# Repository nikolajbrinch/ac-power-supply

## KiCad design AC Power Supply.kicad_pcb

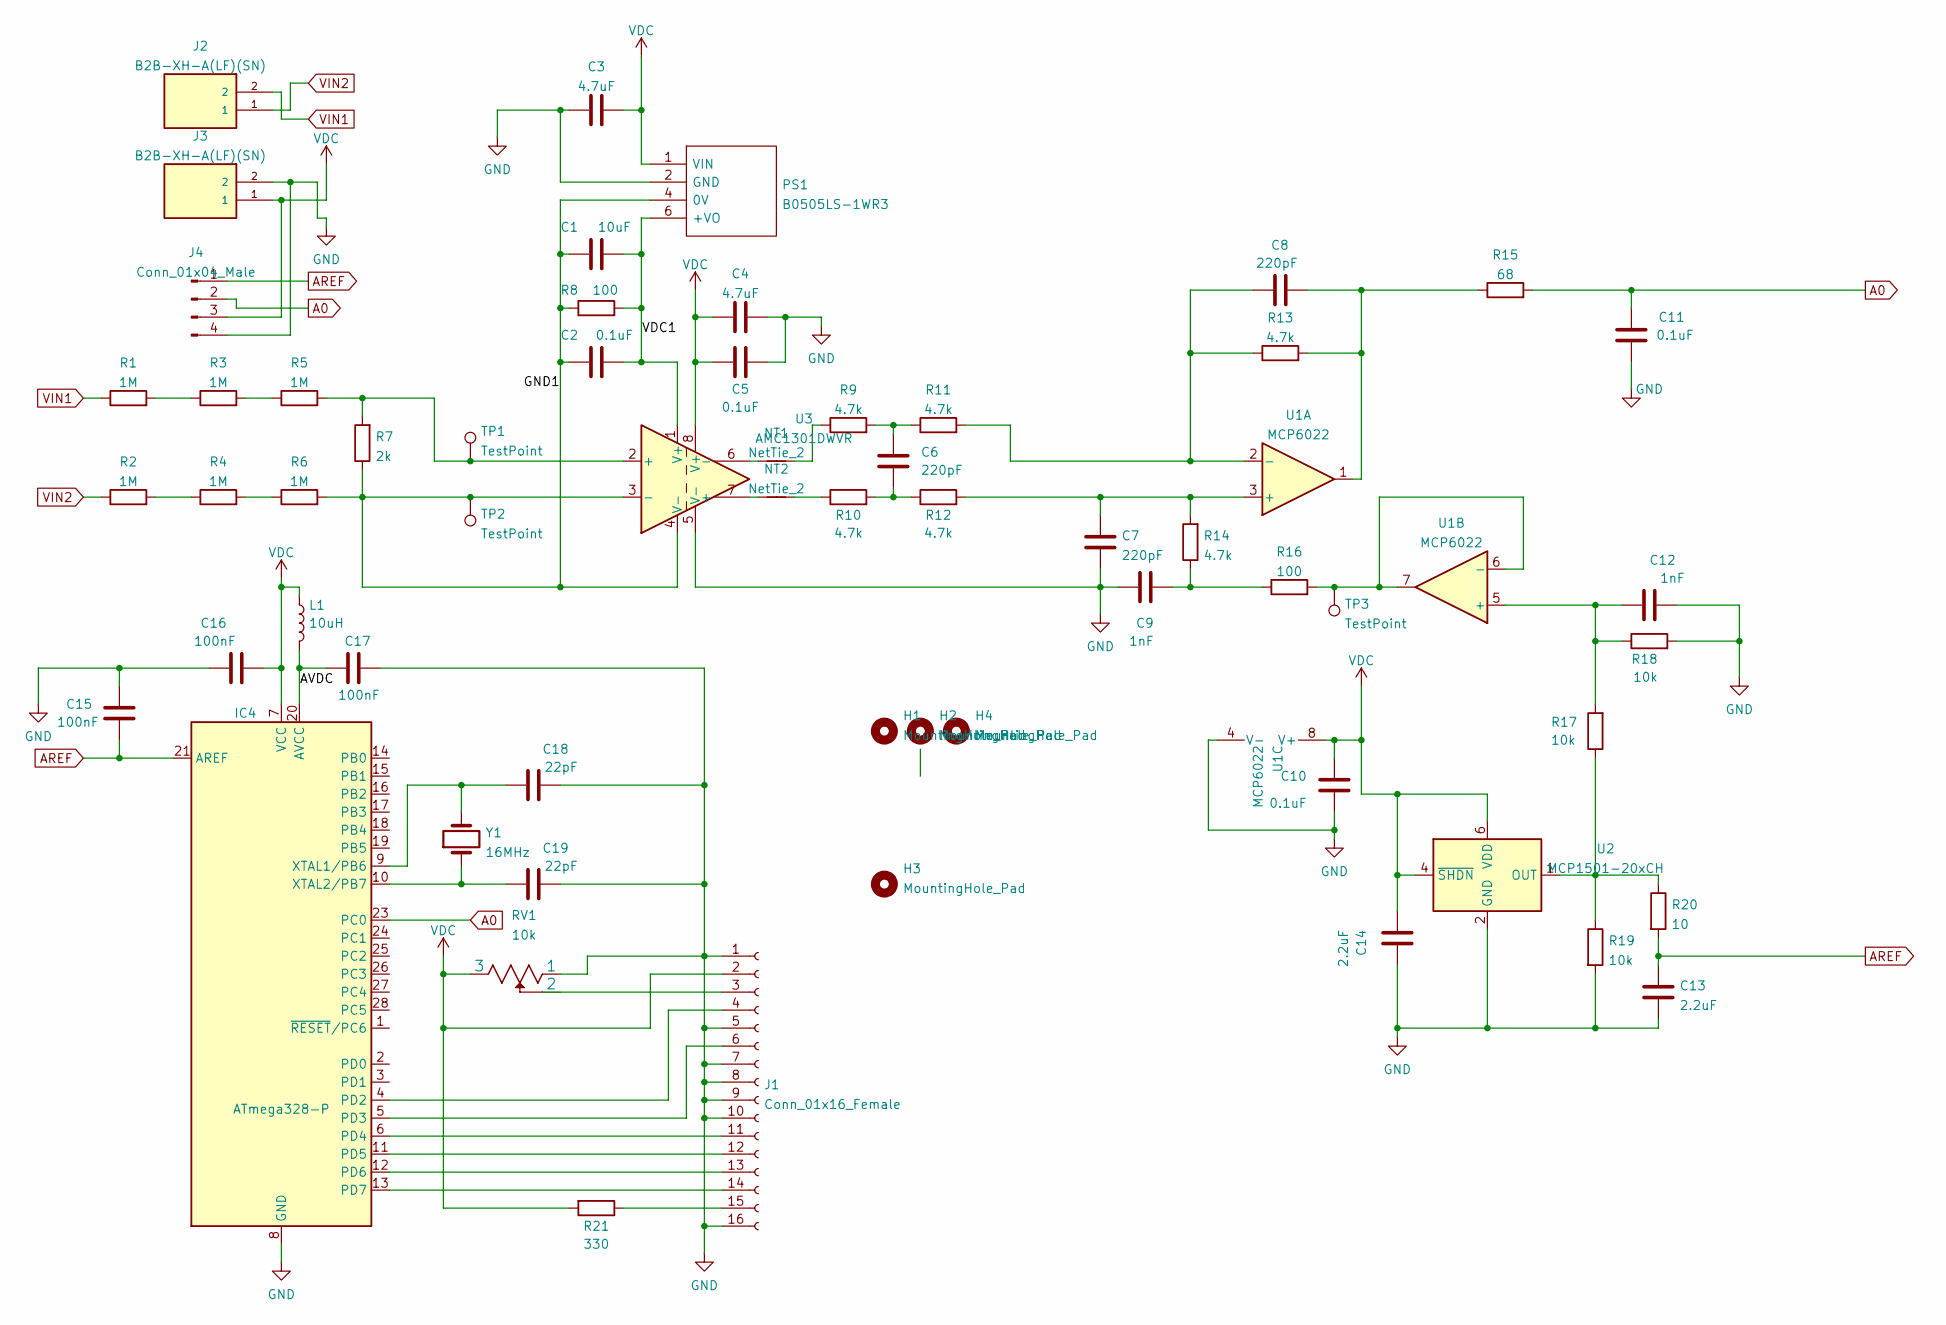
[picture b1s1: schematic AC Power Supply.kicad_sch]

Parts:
C1: 10uF; C_0805_2012Metric_Pad1.18x1.45mm_HandSolder
C2, C5, C10, C11: 0.1uF; C_0805_2012Metric_Pad1.18x1.45mm_HandSolder
C3, C4: 4.7uF; C_0805_2012Metric_Pad1.18x1.45mm_HandSolder
C6, C7, C8: 220pF; C_0805_2012Metric_Pad1.18x1.45mm_HandSolder
C9, C12: 1nF; C_0805_2012Metric_Pad1.18x1.45mm_HandSolder
C13, C14: 2.2uF; C_0805_2012Metric_Pad1.18x1.45mm_HandSolder
C15, C16, C17: 100nF; C_0805_2012Metric_Pad1.18x1.45mm_HandSolder
C18, C19: 22pF; C_0805_2012Metric_Pad1.18x1.45mm_HandSolder
H1, H2, H3, H4: MountingHole_Pad; MountingHole_2.7mm_M2.5_DIN965
IC4: ATmega328-P; DIP-28_W7.62mm_Socket_LongPads
J1: Conn_01x16_Female; PinSocket_1x16_P2.54mm_Vertical
J2, J3: B2B-XH-A(LF)(SN); JST_B2B-XH-A(LF)(SN)
J4: Conn_01x04_Male; PinHeader_1x04_P2.54mm_Vertical
L1: 10uH; L_0805_2012Metric_Pad1.15x1.40mm_HandSolder
NT1, NT2: NetTie_2; NetTie-2_THT_Pad0.3mm
PS1: B0505LS-1WR3; CONV_B0505LS-1WR3; Manufacturer_Part_Number B0505LS-1WR3
R1, R2, R3, R4, R5, R6: 1M; R_1206_3216Metric_Pad1.30x1.75mm_HandSolder
R7: 2k; R_1206_3216Metric_Pad1.30x1.75mm_HandSolder
R8: 100; R_1812_4532Metric_Pad1.30x3.40mm_HandSolder
R9, R10, R11, R12, R13, R14: 4.7k; R_0805_2012Metric_Pad1.20x1.40mm_HandSolder
R15: 68; R_0805_2012Metric_Pad1.20x1.40mm_HandSolder
R16: 100; R_0805_2012Metric_Pad1.20x1.40mm_HandSolder
R17, R18, R19: 10k; R_0805_2012Metric_Pad1.20x1.40mm_HandSolder
R20: 10; R_0805_2012Metric_Pad1.20x1.40mm_HandSolder
R21: 330; R_0805_2012Metric_Pad1.20x1.40mm_HandSolder
RV1: 10k; 64WR10KLF
TP1, TP2, TP3: TestPoint; TestPoint_THTPad_D1.0mm_Drill0.5mm
U1: MCP6022; SOIC-8_3.9x4.9mm_P1.27mm
U2: MCP1501-20xCH; SOT-23-6_Handsoldering
U3: AMC1301DWVR
Y1: 16MHz; Crystal_HC49-4H_Vertical

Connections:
/AVDC: C17.1, IC4.20 (AVCC), L1.2
/GND1: C1.1, C2.1, PS1.4 (0V), R6.2, R7.1, R8.1, TP2.1, U3.3 (-), U3.4 (V-)
/VDC1: C1.2, C2.2, PS1.6 (+VO), R8.2, U3.1 (V+)
A0: C11.2, IC4.23 (PC0), J4.2, R15.2
AREF: C13.1, C15.2, IC4.21 (AREF), J4.1, R20.2
GND: C3.1, C4.1, C5.1, C7.2, C9.1, C10.1, C11.1, C12.2, C13.2, C14.1, C15.1, C16.1, C17.2, C18.2, C19.2, IC4.8 (GND), IC4.22 (GND), J1.1, J1.5, J1.7, J1.8, J1.9, J1.10, J1.16, J3.2, J4.4, PS1.2 (GND), R18.2, R19.2, RV1.1, U1.4 (V-), U2.2 (GND), U2.3 (GND), U2.5 (GND), U3.5 (V-); also elsewhere on the board
unnamed 6: C6.1, R9.2, R11.1; also elsewhere on the board
unnamed 7: C6.2, R10.2, R12.1; also elsewhere on the board
unnamed: C7.1, R12.2, R14.2, U1.3 (+)
unnamed: C8.1, R11.2, R13.1, U1.2 (-)
unnamed: C8.2, R13.2, R15.1, U1.1
unnamed: C9.2, R14.1, R16.1
unnamed: C12.1, R17.2, R18.1, U1.5 (+)
unnamed: C18.1, IC4.9 (XTAL1/PB6), Y1.2
unnamed: C19.1, IC4.10 (XTAL2/PB7), Y1.1
unnamed 15: IC4.4 (PD2), J1.4; also elsewhere on the board
unnamed 16: IC4.5 (PD3), J1.6; also elsewhere on the board
unnamed 17: IC4.6 (PD4), J1.11; also elsewhere on the board
unnamed 18: IC4.11 (PD5), J1.12; also elsewhere on the board
unnamed 19: IC4.12 (PD6), J1.13; also elsewhere on the board
unnamed 20: IC4.13 (PD7), J1.14; also elsewhere on the board
unnamed 21: J1.3, RV1.2; also elsewhere on the board
unnamed 22: J1.15, R21.1; also elsewhere on the board
unnamed: NT1.1, U3.6 (-)
unnamed: NT1.2, R9.1
unnamed: NT2.1, U3.7 (+)
unnamed: NT2.2, R10.1
unnamed: R1.2, R3.1
unnamed: R2.2, R4.1
unnamed: R3.2, R5.1
unnamed: R4.2, R6.1
unnamed: R5.2, R7.2, TP1.1, U3.2 (+)
unnamed: R16.2, TP3.1, U1.6 (-), U1.7
unnamed: R17.1, R19.1, R20.1, U2.1 (OUT)
VDC: C3.2, C4.2, C5.2, C10.2, C14.2, C16.2, IC4.7 (VCC), J1.2, J3.1, J4.3, L1.1, PS1.1 (VIN), R21.2, RV1.3, U1.8 (V+), U2.4 (~SHDN), U2.6 (VDD), U3.8 (V+); also elsewhere on the board
VIN1: J2.2, R1.1
VIN2: J2.1, R2.1

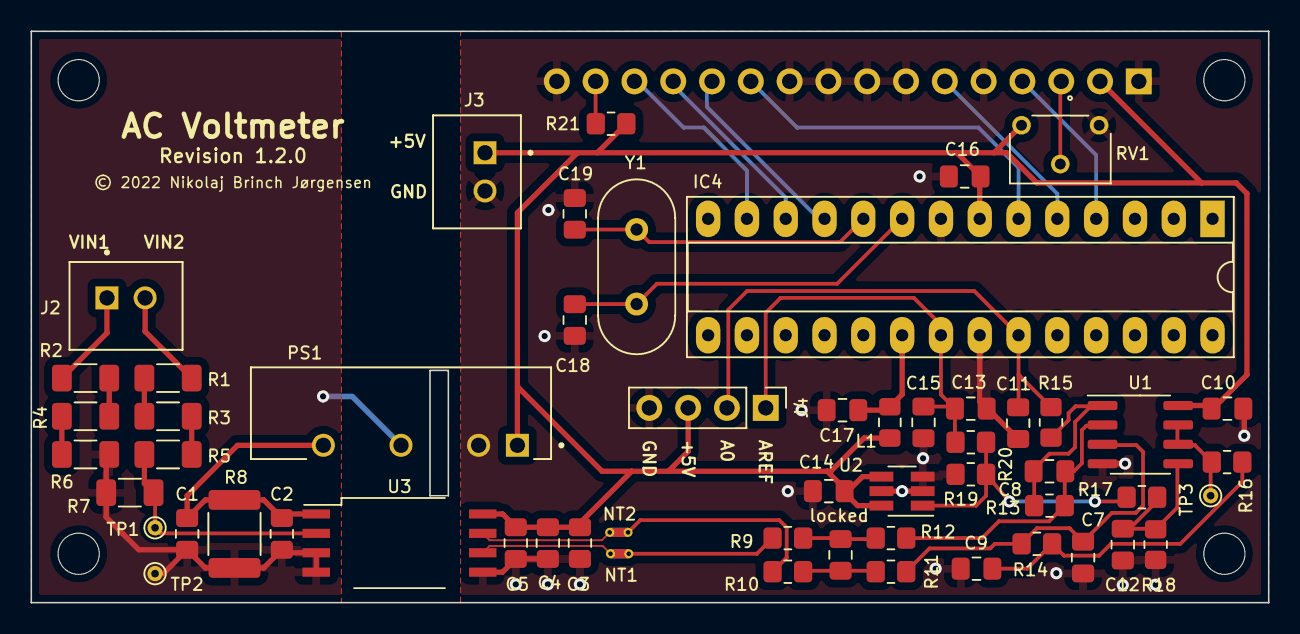
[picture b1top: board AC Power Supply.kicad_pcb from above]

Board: 2 copper layers, 81.0 x 37.4 mm, 61 parts (1 on the bottom side), 37 nets.

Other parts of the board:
locked: 220pF; C_0805_2012Metric_Pad1.18x1.45mm_HandSolder
locked#2: Conn_01x16_Female; PinSocket_1x16_P2.54mm_Vertical

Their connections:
GND: locked#2.1, locked#2.5, locked#2.7, locked#2.8, locked#2.9, locked#2.10, locked#2.16; also elsewhere on the board
unnamed 6: locked.1; also elsewhere on the board
unnamed 7: locked.2; also elsewhere on the board
unnamed 15: locked#2.4; also elsewhere on the board
unnamed 16: locked#2.6; also elsewhere on the board
unnamed 17: locked#2.11; also elsewhere on the board
unnamed 18: locked#2.12; also elsewhere on the board
unnamed 19: locked#2.13; also elsewhere on the board
unnamed 20: locked#2.14; also elsewhere on the board
unnamed 21: locked#2.3; also elsewhere on the board
unnamed 22: locked#2.15; also elsewhere on the board
VDC: locked#2.2; also elsewhere on the board

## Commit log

2022-02-22 FIrst revision
2022-02-24 Revision 1.2.0

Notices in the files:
AC Power Supply.kicad_pcb:
© 2022 Nikolaj Brinch Jørgensen
parts and their libraries:
Copyright 2021 Accelerated Designs. All rights reserved.
